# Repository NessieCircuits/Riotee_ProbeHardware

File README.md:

# Riotee Probe Hardware Design Files

The Riotee probe lets you program a Riotee module that is soldered onto your PCB or plugged into a breadboard. It has a standard 10-pin 0.1" connector compatible with the popular Tag-Connect cables that allow in-circuit debugging with a very small footprint.

Latest design files:
 - [Schematics](https://www.riotee.nessie-circuits.de/artifacts/probe_hardware/latest/schematics.pdf)
 - [Layout](https://www.riotee.nessie-circuits.de/artifacts/probe_hardware/latest/pcb.pdf)
 - [Assembly plan](https://www.riotee.nessie-circuits.de/artifacts/probe_hardware/latest/assembly.pdf)
 - [3D rendering](https://www.riotee.nessie-circuits.de/artifacts/probe_hardware/latest/3drendering.png)
 - [Gerber](https://www.riotee.nessie-circuits.de/artifacts/probe_hardware/latest/gerber.zip)
 - [BOM](https://www.riotee.nessie-circuits.de/artifacts/probe_hardware/latest/bom.csv)

Specification:
 - Custom debug probe for in-circuit programming/debugging of Riotee modules
 - USB-C connector for connection to a PC
 - Raspberry Pi RP2040 controller handles programming/debugging
 - CMSIS-DAP compatible: Supports programming of the Riotee module via pyOCD/OpenOCD
 - Makes UART output from Riotee module available via USB

## Firmware

The probe has a dedicated controller (Raspberry Pi RP2040) that manages the upload of new firmware to the Riotee device as well as the communication with a PC. The firmware running on the RP2040 is hosted in [this repository](https://github.com/NessieCircuits/Riotee_ProbeFirmware). To upgrade the firmware on the Riotee probe, connect a wire from one of the ground pins to the test pad labelled 'USB_BOOT' on the bottom of the board, while plugging in the USB cable. A removable storage drive should appear on your PC. Drop a UF2 compatible binary into the drive.

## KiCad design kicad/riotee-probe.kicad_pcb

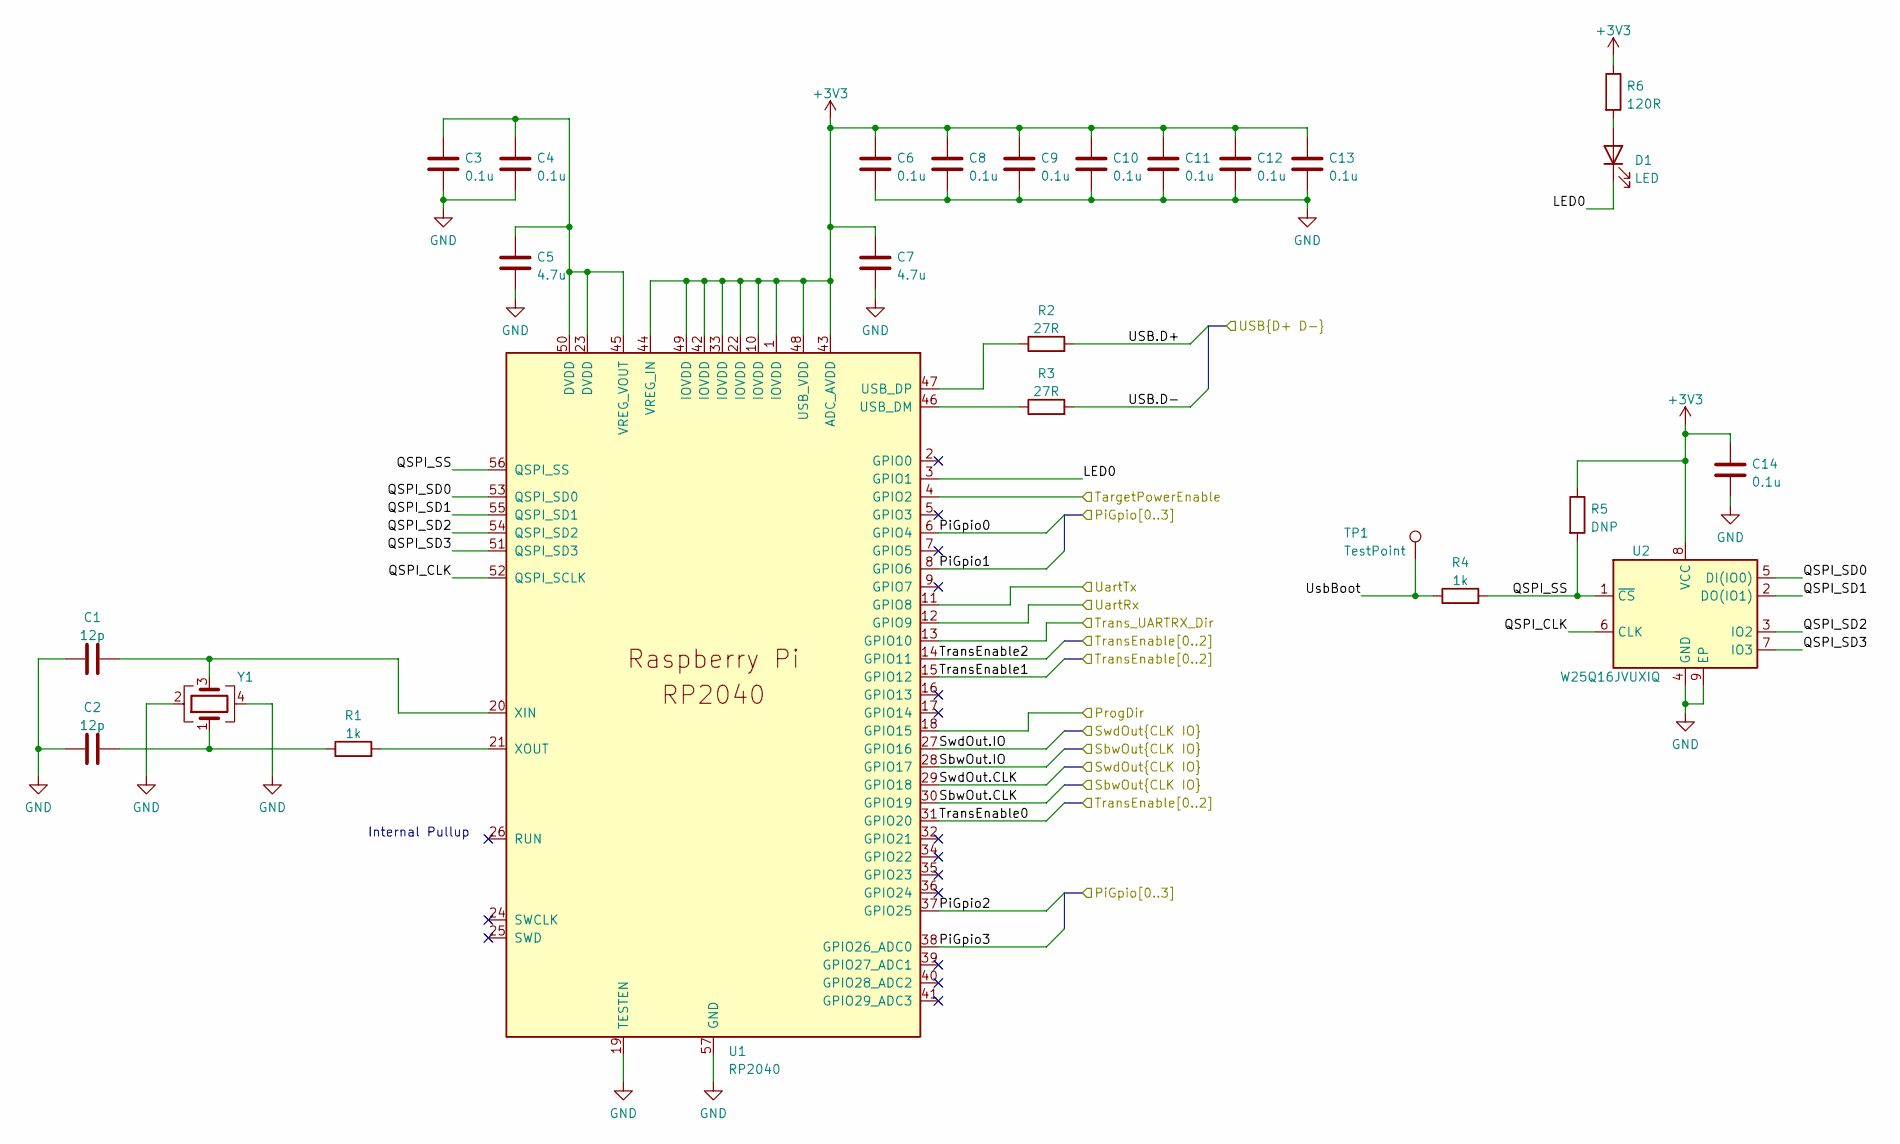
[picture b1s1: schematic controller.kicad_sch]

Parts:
C1, C2: 12p; C_0402_1005Metric; MPN 04025A120JAT2A
C3, C4, C6, C8, C9, C10, C11, C12, C13, C14: 0.1u; C_0402_1005Metric; MPN CL05A104KA5NNNC
C5, C7: 4.7u; C_0402_1005Metric; MPN CL05A475MP5NRNC
D1: LED; LED_0402_1005Metric; MPN QBLP595-AG1
R1, R4: 1k; R_0402_1005Metric; MPN WR04X1001FTL
R2, R3: 27R; R_0402_1005Metric; MPN CR0402-FX-27R0GLF
R5: DNP; R_0402_1005Metric
R6: 120R; R_0402_1005Metric; MPN CR0402-FX-1200GLF
TP1: TestPoint; TestPoint_Pad_D1.0mm
U1: RP2040; RP_RP2040; MPN RP2040
U2: W25Q16JVUXIQ; WB_UX8; MPN W25Q16JVUXIQ
Y1: Crystal_GND24; RALTRON_RH100; MPN RH100-12.000-18-2030-TR

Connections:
+3V3: C6.1, C7.1, C8.1, C9.1, C10.1, C11.1, C12.1, C13.1, C14.1, R5.1, R6.1, U1.1 (IOVDD), U1.10 (IOVDD), U1.22 (IOVDD), U1.33 (IOVDD), U1.42 (IOVDD), U1.43 (ADC_AVDD), U1.44 (VREG_IN), U1.48 (USB_VDD), U1.49 (IOVDD), U2.8 (VCC); also elsewhere on the board
/Connectors/PiGpio0: U1.6 (GPIO4); also elsewhere on the board
/Connectors/PiGpio1: U1.8 (GPIO6); also elsewhere on the board
/Connectors/PiGpio2: U1.37 (GPIO25); also elsewhere on the board
/Connectors/PiGpio3: U1.38 (GPIO26_ADC0); also elsewhere on the board
/Connectors/TargetPowerEnable: U1.4 (GPIO2); also elsewhere on the board
/Controller/LED0: D1.1 (K), U1.3 (GPIO1)
/Controller/ProgDir: U1.18 (GPIO15); also elsewhere on the board
/Controller/QSPI_CLK: U1.52 (QSPI_SCLK), U2.6 (CLK)
/Controller/QSPI_SD0: U1.53 (QSPI_SD0), U2.5 (DI(IO0))
/Controller/QSPI_SD1: U1.55 (QSPI_SD1), U2.2 (DO(IO1))
/Controller/QSPI_SD2: U1.54 (QSPI_SD2), U2.3 (IO2)
/Controller/QSPI_SD3: U1.51 (QSPI_SD3), U2.7 (IO3)
/Controller/QSPI_SS: R4.2, R5.2, U1.56 (QSPI_SS), U2.1 (~CS)
/Controller/SbwOut.CLK: U1.30 (GPIO19); also elsewhere on the board
/Controller/SbwOut.IO: U1.28 (GPIO17); also elsewhere on the board
/Controller/SwdOut.CLK: U1.29 (GPIO18); also elsewhere on the board
/Controller/SwdOut.IO: U1.27 (GPIO16); also elsewhere on the board
/Controller/TransEnable0: U1.31 (GPIO20); also elsewhere on the board
/Controller/TransEnable1: U1.15 (GPIO12); also elsewhere on the board
/Controller/TransEnable2: U1.14 (GPIO11); also elsewhere on the board
/Controller/Trans_UARTRX_Dir: U1.13 (GPIO10); also elsewhere on the board
/Controller/USB.D+: R2.2; also elsewhere on the board
/Controller/USB.D-: R3.2; also elsewhere on the board
/Controller/UartRx: U1.12 (GPIO9); also elsewhere on the board
/Controller/UartTx: U1.11 (GPIO8); also elsewhere on the board
/Controller/UsbBoot: R4.1, TP1.1
GND: C1.1, C2.2, C3.2, C4.2, C5.2, C6.2, C7.2, C8.2, C9.2, C10.2, C11.2, C12.2, C13.2, C14.2, U1.19 (TESTEN), U1.57 (GND), U2.4 (GND), U2.9 (EP), Y1.2, Y1.4; also elsewhere on the board
unnamed: C2.1, R1.1, Y1.1
unnamed: D1.2 (A), R6.2
unnamed: R3.1, U1.46 (USB_DM)
unnamed: R2.1, U1.47 (USB_DP)
unnamed: C3.1, C4.1, C5.1, U1.23 (DVDD), U1.45 (VREG_VOUT), U1.50 (DVDD)
unnamed: C1.2, U1.20 (XIN), Y1.3
unnamed: R1.2, U1.21 (XOUT)

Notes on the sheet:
Internal Pullup

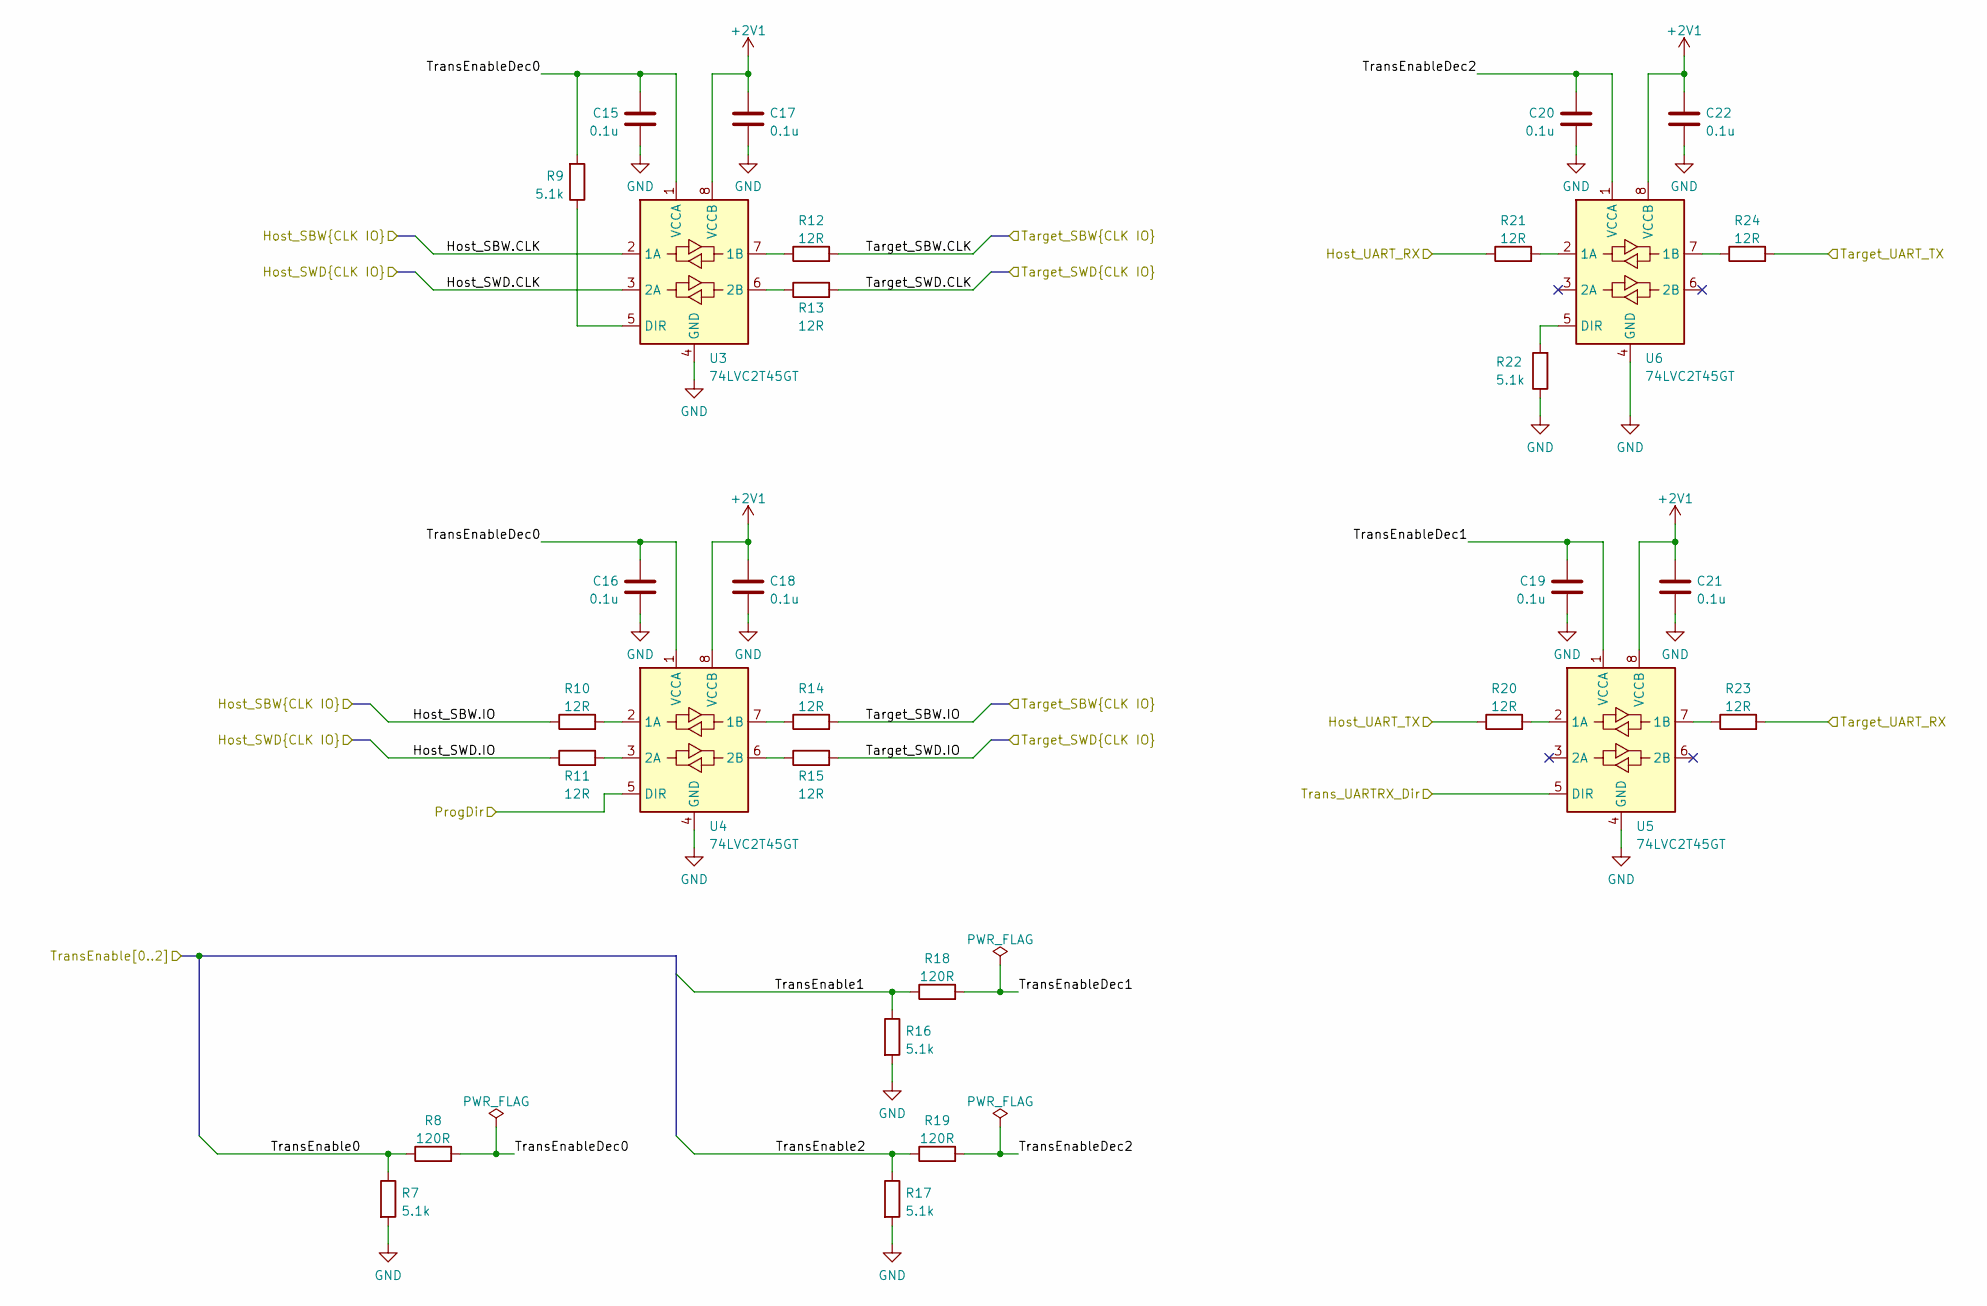
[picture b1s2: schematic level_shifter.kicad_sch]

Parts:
C15, C16, C17, C18, C19, C20, C21, C22: 0.1u; C_0402_1005Metric; MPN CL05A104KA5NNNC
R7, R9, R16, R17, R22: 5.1k; R_0402_1005Metric; MPN CR0402-FX-5101GLF
R8, R18, R19: 120R; R_0402_1005Metric; MPN CR0402-FX-1200GLF
R10, R11, R12, R13, R14, R15, R20, R21, R23, R24: 12R; R_0402_1005Metric; MPN RMCF0402FT12R0
U3, U4, U5, U6: 74LVC2T45GT; NXP_SOT833-1; MPN 74LVC2T45GT,115

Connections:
+2V1: C17.1, C18.1, C21.1, C22.1, U3.8 (VCCB), U4.8 (VCCB), U5.8 (VCCB), U6.8 (VCCB); also elsewhere on the board
/Connectors/Target_SBW.CLK: R12.2; also elsewhere on the board
/Connectors/Target_SBW.IO: R14.2; also elsewhere on the board
/Connectors/Target_SWD.CLK: R13.2; also elsewhere on the board
/Connectors/Target_SWD.IO: R15.2; also elsewhere on the board
/Connectors/Target_UART_RX: R23.2; also elsewhere on the board
/Connectors/Target_UART_TX: R24.2; also elsewhere on the board
/Controller/ProgDir: U4.5 (DIR); also elsewhere on the board
/Controller/SbwOut.CLK: U3.2 (1A); also elsewhere on the board
/Controller/SbwOut.IO: R10.1; also elsewhere on the board
/Controller/SwdOut.CLK: U3.3 (2A); also elsewhere on the board
/Controller/SwdOut.IO: R11.1; also elsewhere on the board
/Controller/TransEnable0: R7.1, R8.1; also elsewhere on the board
/Controller/TransEnable1: R16.1, R18.1; also elsewhere on the board
/Controller/TransEnable2: R17.1, R19.1; also elsewhere on the board
/Controller/Trans_UARTRX_Dir: U5.5 (DIR); also elsewhere on the board
/Controller/UartRx: R21.1; also elsewhere on the board
/Controller/UartTx: R20.1; also elsewhere on the board
/LevelShifter/TransEnableDec0: C15.2, C16.2, R8.2, R9.2, U3.1 (VCCA), U4.1 (VCCA)
/LevelShifter/TransEnableDec1: C19.2, R18.2, U5.1 (VCCA)
/LevelShifter/TransEnableDec2: C20.2, R19.2, U6.1 (VCCA)
GND: C15.1, C16.1, C17.2, C18.2, C19.1, C20.1, C21.2, C22.2, R7.2, R16.2, R17.2, R22.1, U3.4 (GND), U4.4 (GND), U5.4 (GND), U6.4 (GND); also elsewhere on the board
unnamed: R12.1, U3.7 (1B)
unnamed: R13.1, U3.6 (2B)
unnamed: R9.1, U3.5 (DIR)
unnamed: R10.2, U4.2 (1A)
unnamed: R14.1, U4.7 (1B)
unnamed: R11.2, U4.3 (2A)
unnamed: R15.1, U4.6 (2B)
unnamed: R20.2, U5.2 (1A)
unnamed: R23.1, U5.7 (1B)
unnamed: R21.2, U6.2 (1A)
unnamed: R24.1, U6.7 (1B)
unnamed: R22.2, U6.5 (DIR)

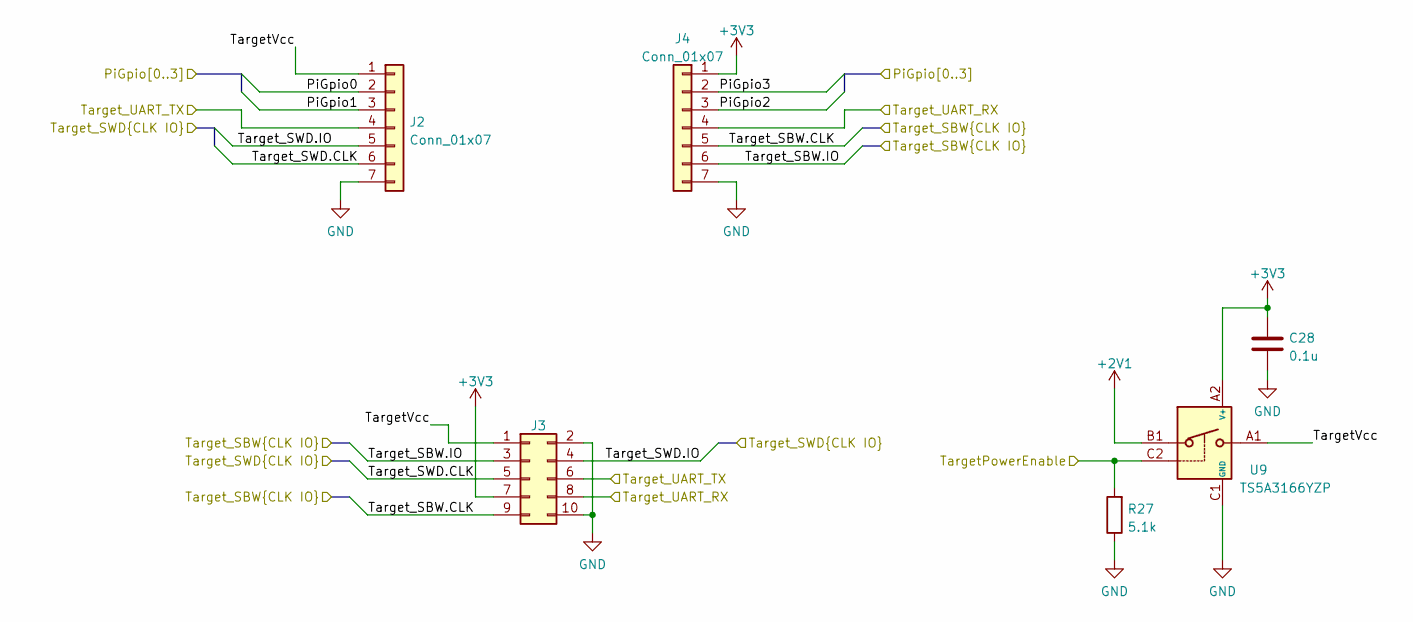
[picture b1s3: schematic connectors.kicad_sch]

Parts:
C28: 0.1u; C_0402_1005Metric; MPN CL05A104KA5NNNC
J2, J4: Conn_01x07; PinHeader_1x07_P2.54mm_Plain
J3: Conn_02x05_Odd_Even; IDC-Header_2x05_P2.54mm_Vertical_SMD; MPN AWHW 10G-SMD
R27: 5.1k; R_0402_1005Metric; MPN CR0402-FX-5101GLF
U9: TS5A3166YZP; TI_YZP0005; MPN TS5A3166YZP

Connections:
+2V1: U9.B1; also elsewhere on the board
+3V3: C28.1, J3.7, J4.1, U9.A2 (V+); also elsewhere on the board
/Connectors/PiGpio0: J2.2; also elsewhere on the board
/Connectors/PiGpio1: J2.3; also elsewhere on the board
/Connectors/PiGpio2: J4.3; also elsewhere on the board
/Connectors/PiGpio3: J4.2; also elsewhere on the board
/Connectors/TargetPowerEnable: R27.2, U9.C2; also elsewhere on the board
/Connectors/TargetVcc: J2.1, J3.1, U9.A1
/Connectors/Target_SBW.CLK: J3.9, J4.5; also elsewhere on the board
/Connectors/Target_SBW.IO: J3.3, J4.6; also elsewhere on the board
/Connectors/Target_SWD.CLK: J2.6, J3.5; also elsewhere on the board
/Connectors/Target_SWD.IO: J2.5, J3.4; also elsewhere on the board
/Connectors/Target_UART_RX: J3.8, J4.4; also elsewhere on the board
/Connectors/Target_UART_TX: J2.4, J3.6; also elsewhere on the board
GND: C28.2, J2.7, J3.2, J3.10, J4.7, R27.1, U9.C1 (GND); also elsewhere on the board

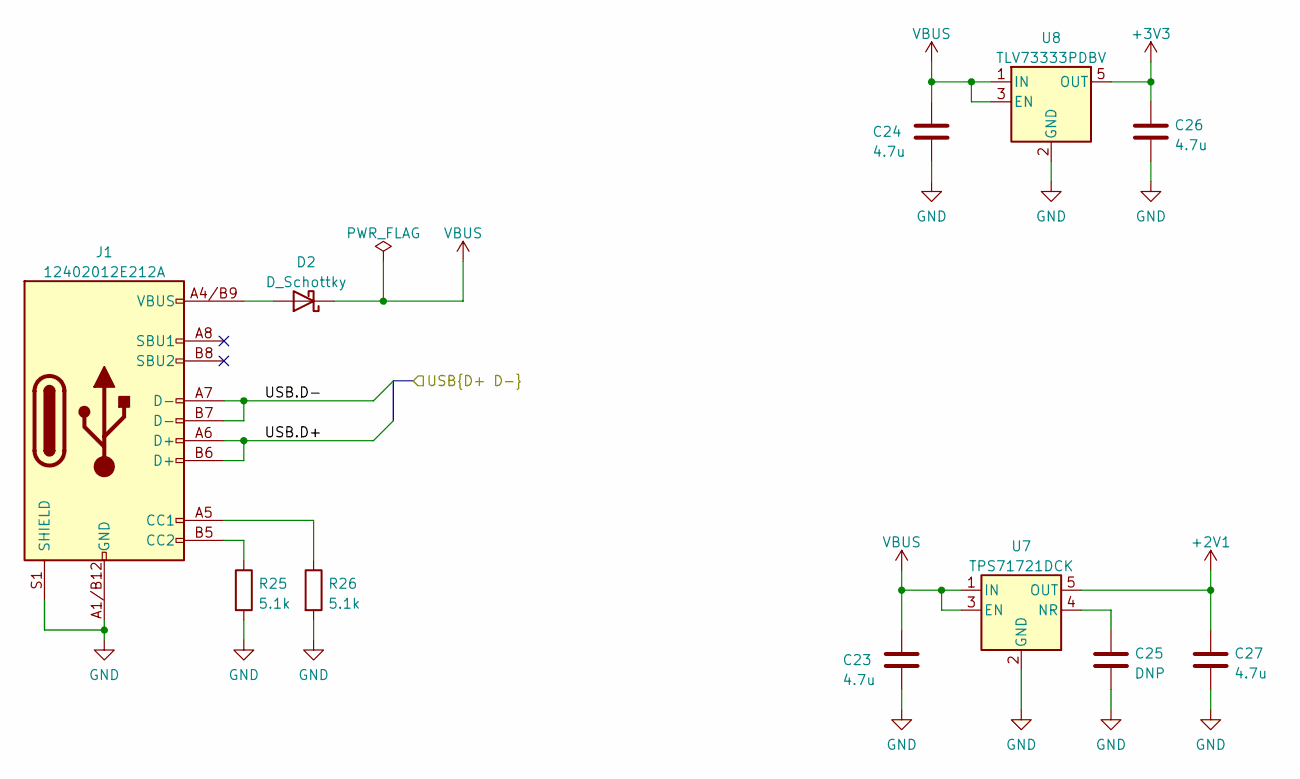
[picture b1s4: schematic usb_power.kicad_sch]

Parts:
C23, C24, C26, C27: 4.7u; C_0402_1005Metric; MPN CL05A475MP5NRNC
C25: DNP; C_0402_1005Metric
D2: D_Schottky; D_SOD-523; MPN RB521S30T1G
J1: 12402012E212A; AMPH_12402012E212A; MPN 12402012E212A
R25, R26: 5.1k; R_0402_1005Metric; MPN CR0402-FX-5101GLF
U7: TPS71721DCK; TI_DCK0005A; MPN TPS71721DCK
U8: TLV73333PDBV; TI_DBV0005A; MPN TLV73333PDBV

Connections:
+2V1: C27.1, U7.5 (OUT); also elsewhere on the board
+3V3: C26.1, U8.5 (OUT); also elsewhere on the board
/Controller/USB.D+: J1.A6 (D+), J1.B6 (D+); also elsewhere on the board
/Controller/USB.D-: J1.A7 (D-), J1.B7 (D-); also elsewhere on the board
GND: C23.2, C24.2, C25.2, C26.2, C27.2, J1.A1/B12 (GND), J1.B1/A12 (GND), J1.S1 (SHIELD), R25.2, R26.2, U7.2 (GND), U8.2 (GND); also elsewhere on the board
unnamed: D2.2 (A), J1.A4/B9 (VBUS), J1.B4/A9 (VBUS)
unnamed: J1.A5 (CC1), R26.1
unnamed: J1.B5 (CC2), R25.1
unnamed: C25.1, U7.4 (NR)
VBUS: C23.1, C24.1, D2.1 (K), U7.1 (IN), U7.3 (EN), U8.1 (IN), U8.3 (EN)

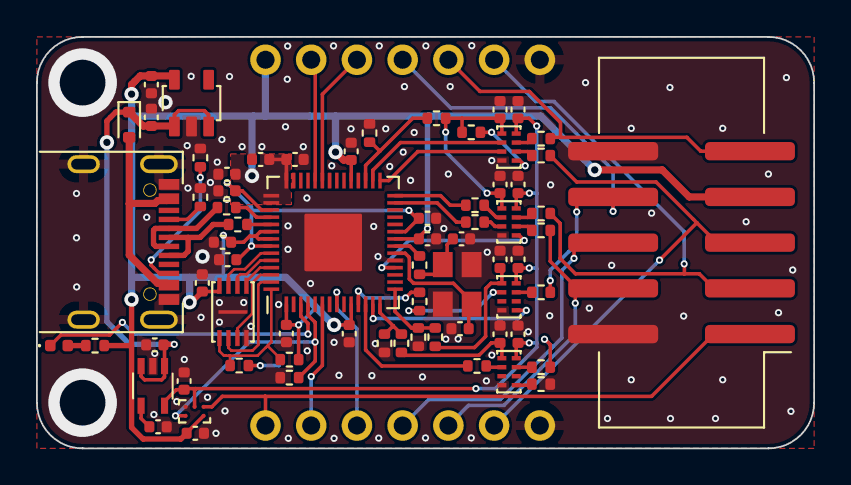
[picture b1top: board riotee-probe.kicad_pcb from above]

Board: 4 copper layers, 43.2 x 22.9 mm, 72 parts (1 on the bottom side), 63 nets.

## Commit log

2023-01-18 add GH workflow for kibot
2023-01-19 move generated outputs to 'latest' dir on server
2023-01-19 update kicad library
2023-01-19 add kibot 3dmodel build
2023-01-19 remove obsolete rendering from repo
2023-01-19 update board footprints
2023-01-19 make gh action checkout submodules, too
2023-01-22 add fourth level converter for simultaneous programming + TX/RX
2023-01-22 add GH workflow for ERC/DRC with kibot
2023-01-22 add GH status badge to README
2023-01-22 fix build workflow config file name
2023-01-31 add assembly plan to CI/CD build
2023-02-02 adjust values of level translator series resistors
2023-02-20 replace target supply diode with analog switch
2023-02-20 add MPNs in schematics
2023-02-21 fix pulldown value
2023-04-05 change to 4 layer board
2023-04-10 update footprints and add component description to BOM
2023-04-14 add conformity marks and refine BOM settings
2023-04-15 fix position of one pin header
2023-05-06 migrate project to kicad 7
2023-05-06 add config for kikit panelization
2024-06-26 update to kicad 8
2024-10-15 generate bom and gerber in github workflow with kibot
